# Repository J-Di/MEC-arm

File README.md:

<h1>MEC-Arm</h1>

## Overview
MEC-Arm is a six degree of freedom robotic arm which is currently being designed from scratch by 2 students team. The team is composed of a mechanical and electrical engineering student, working together to realize this shared personal project. The overall objective is to create a fully functional, precise, and practical arm, while creating many of the required components from scratch along the way. This repository contains both the mechanical and the electrical side of the project, after all, this is a **M**echanical **E**lectrical **C**ollaboration -Arm :)

Find all the Documentation here: [MEC-Arm Documentation Page](https://j-di.github.io/MEC-arm/)

### Key Features:

#### Arm
- Joint layout: waist (roll), shoulder (pitch), elbow (pitch), 3-axis wrist (roll, pitch, roll)
- Arm weight: TBD
- End effector: gripper, driven by the 7th motor
- Max joint speed: 90 RPM (shoulder)

#### Actuation

- Actuators: 7× brushless motors with custom cycloidal gearboxes
- Gear ratios: 19:1, 25:1, 15:1
- Motor control: FOC at every joint
- Position feedback: on-board magnetic encoders

#### Power & control

- Battery: 6S LiPo, 25.2–18V, TBD mA
- Communication: CAN bus 
- Host: controlled from a raspberry pi

## Timeline

```mermaid
flowchart LR
    subgraph Shared
        A[Requirements defined]
        B[Arm structure decided]
        C[Joint torque calculations]
        D[Motors sourced]
    end

    subgraph Electrical
        E[ESC design]
        H[ESC bring-up and testing]
        P[Power distribution and coordination board]
    end

    subgraph Mechanical
        F[Preliminary arm structure]
        G[Gearbox design]
        I[Joint assembly]
    end

    K[Per-joint gearbox testing]
    L[Torque characterization]
    J[Full arm integration]
    S[Software begins]

    A --> B --> C --> D
    D --> E --> H
    D --> P
    D --> F --> G --> I
    H --> K
    G --> K
    K --> L
    L --> J
    I --> J
    P --> J
    J --> S

    classDef done fill:#2da44e,stroke:#1a7f37,color:#fff
    classDef wip  fill:#d4a72c,stroke:#9a6700,color:#fff
    classDef todo fill:#8c959f,stroke:#57606a,color:#fff
    class A,B,C,D,F done
    class E,G,P wip
    class H,I,J,K,L,S todo
```

🟩 Done · 🟨 In progress · ⬜ Planned

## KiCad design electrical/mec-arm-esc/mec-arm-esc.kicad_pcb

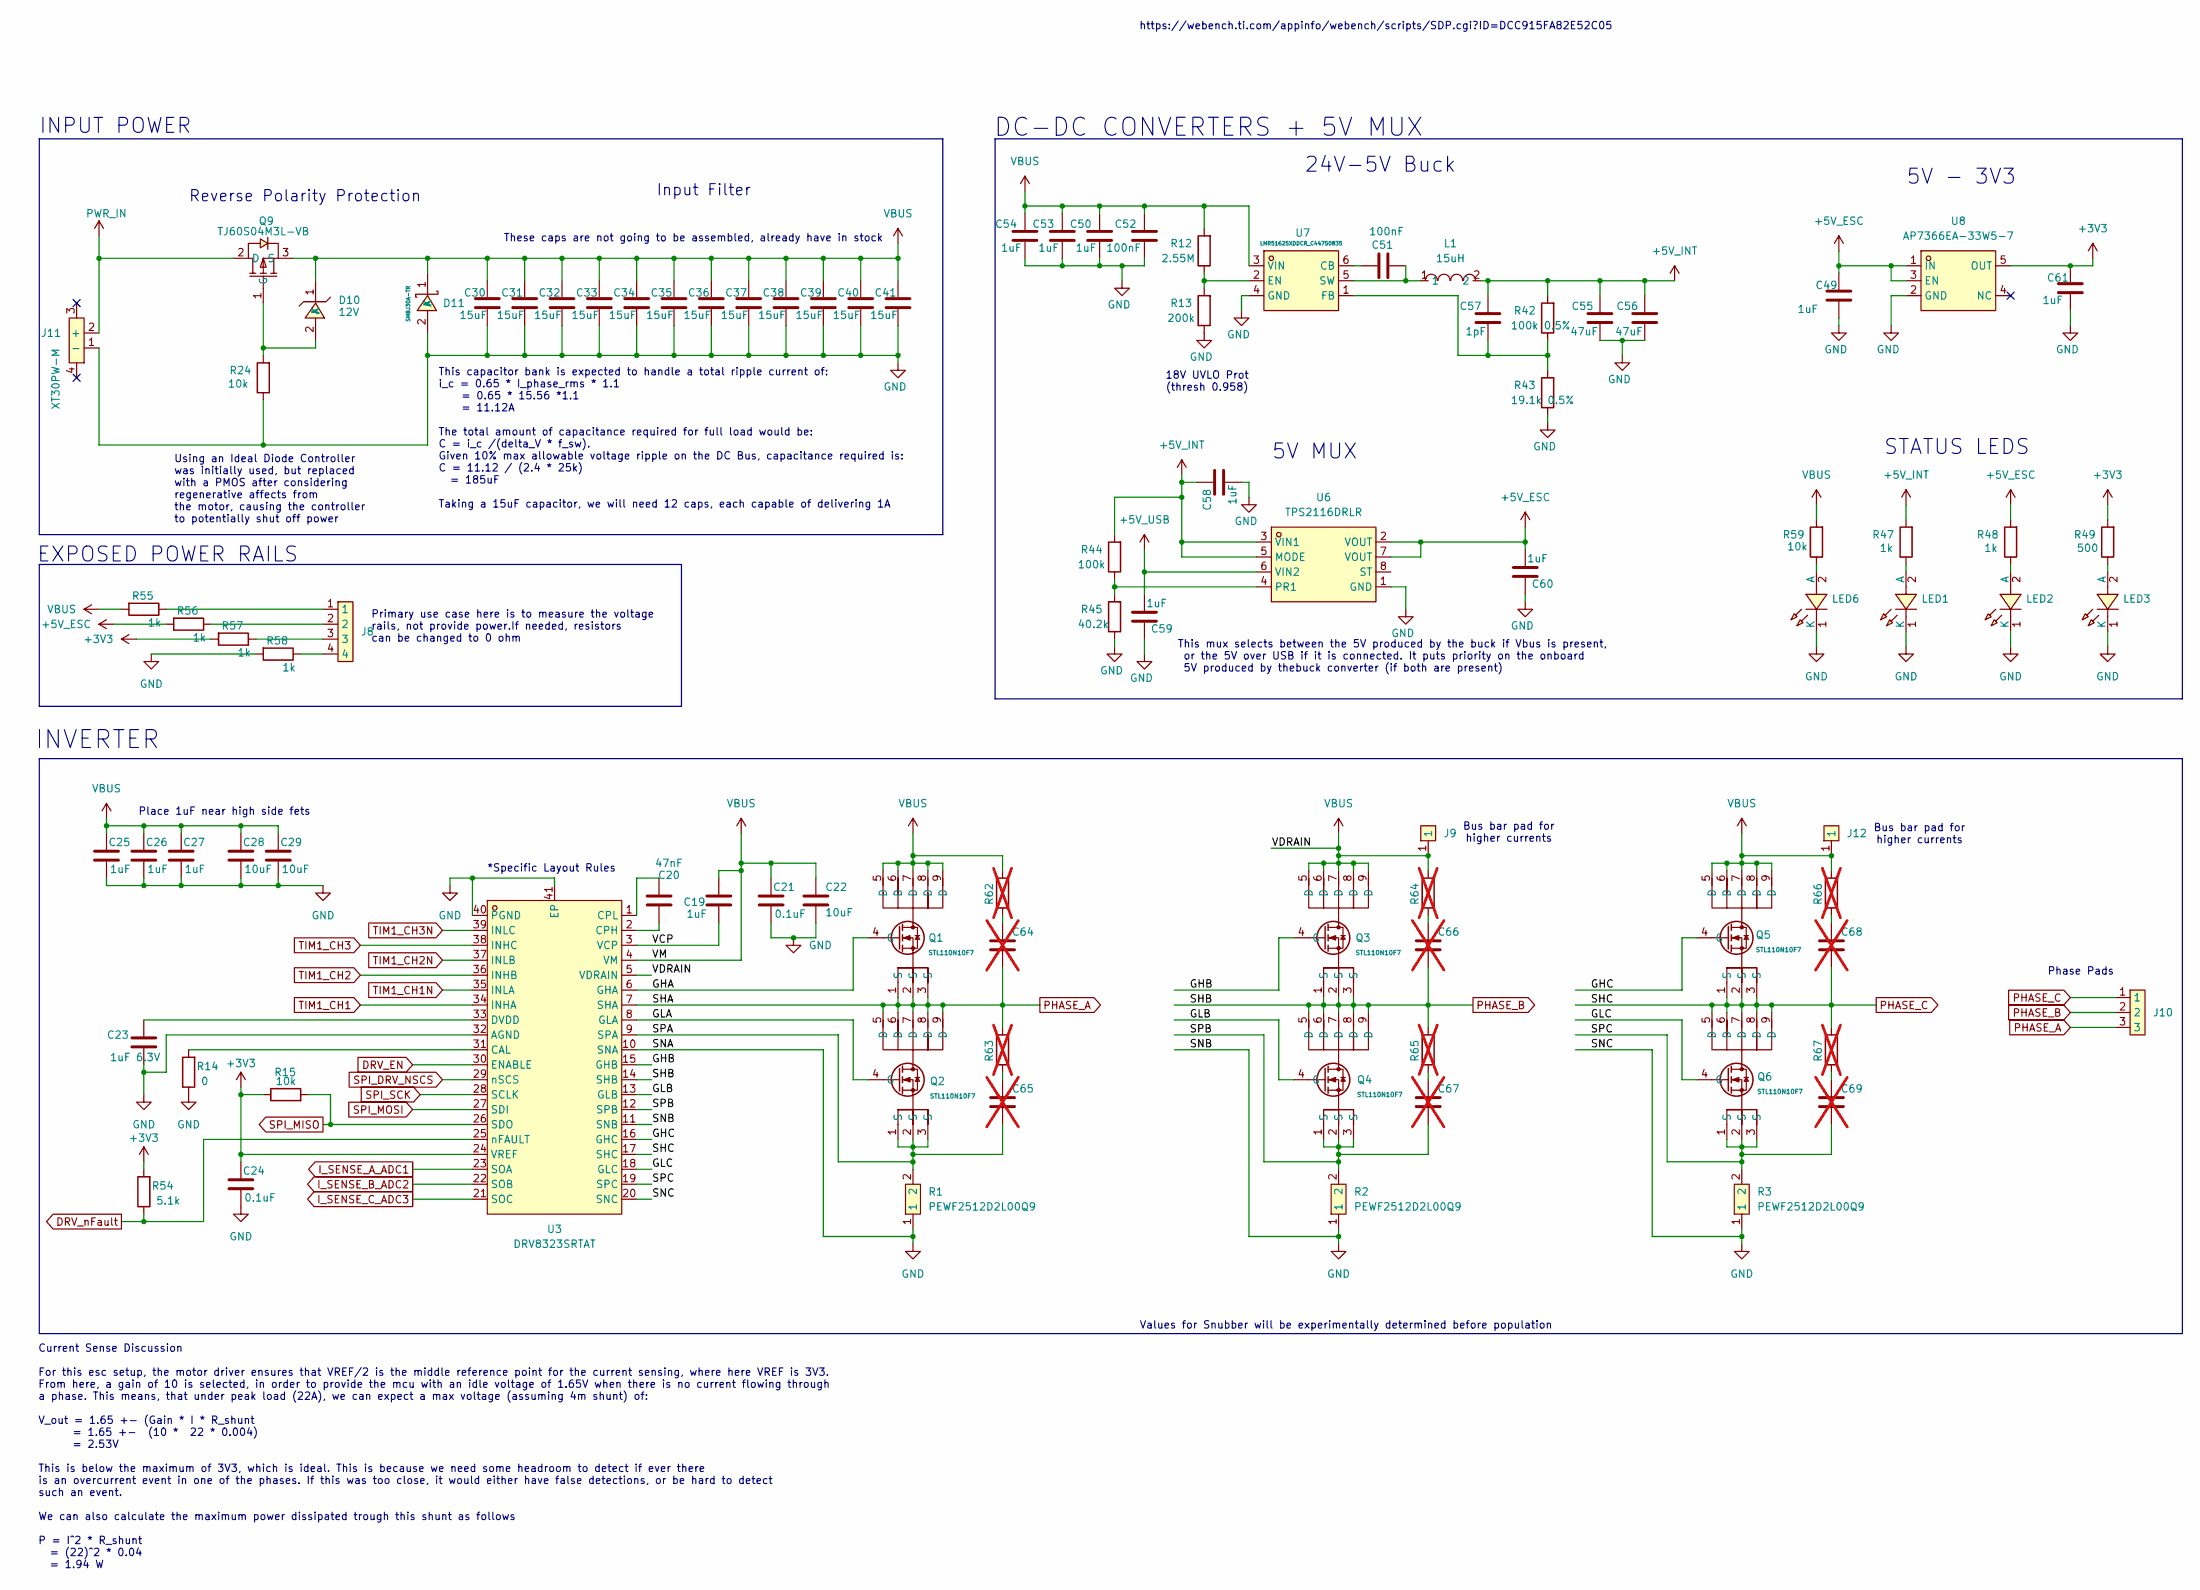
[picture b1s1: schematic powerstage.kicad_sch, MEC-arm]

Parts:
C19: 1uF; C_0603; LCSC Part C14664
C20: 47nF; C_0603; LCSC Part C513577
C21: 0.1uF; C_0603; LCSC Part C14663
C22, C28, C29: 10uF; C_0805; LCSC Part C162422
C23: 1uF 6.3V; C_0603; LCSC Part C2169508
C24: 0.1uF; C_0603; LCSC Part C108079
C25, C26, C27, C50, C53, C54: 1uF; C_0603; LCSC Part C559769
C30: 15uF; C_0805; LCSC Part# C162422
C31, C32, C33, C34, C35, C36, C37, C38, C39, C40, C41: 15uF; C_0805; LCSC Part C162422
C49, C58, C59, C60, C61: 1uF; C_0603; LCSC Part C106248
C51, C52: 100nF; C_0603; LCSC Part C14663
C55, C56: 47uF; C_1210_3225Metric; LCSC Part C77101
C57: 1pF; C_0603; LCSC Part C29936
C64, C65, C66, C67, C68, C69: 10uF; C_0603; not fitted
D10: 12V; SOD-123F_L2.8-W1.8-LS3.7-RD; MPN BZT52C12-13-F; LCSC Part C177013
D11: SMBJ30A-TR; SMB_L4.6-W3.6-LS5.3-RD; MPN SMBJ30A-TR; LCSC Part C133663
J8: TestPadArray1x4
J9: 5x3BusBar Pad
J10: PHASE_PAD
J11: XT30PW-M; CONN-TH_XT30PW-M; MPN XT30PW-M30.G.Y; LCSC Part C431092
J12: 3x3BusBar Pad
L1: 15uH; IND-SMD_L6.0-W6.0_VLS6045EX; MPN VLS6045EX-150M; LCSC Part C404502
LED1, LED2, LED3, LED6: 150060RS75000; LED0603-RD_RED; MPN 150060RS75000; LCSC Part C3030991
Q1, Q2, Q3, Q4, Q5, Q6: STL110N10F7; DFN-8_L5.8-W4.9-P1.27-LS6.0-BL-1; MPN STL110N10F7; LCSC Part C672185
Q9: TJ60S04M3L-VB; TO-252-2_L6.6-W6.1-P4.58-LS9.9-TL; MPN TJ60S04M3L-VB; LCSC Part C7494452
R1, R2, R3: PEWF2512D2L00Q9; RES-SMD_L6.3-W3.2_R2512; MPN PEWF2512D2L00Q9; LCSC Part C19697176
R12: 2.55M; R_0603; LCSC Part C54102347
R13: 200k; R_0603; LCSC Part C2907009
R14: 0; R_0603; LCSC Part C2906974
R15, R24, R59: 10k; R_0603; LCSC Part C98220
R42: 100k 0.5%; R_0603; LCSC Part C122538
R43: 19.1k 0.5%; R_0603; LCSC Part C861184
R44: 100k; R_0603; LCSC Part C2906980
R45: 40.2k; R_0603; LCSC Part C286588
R47, R48, R55, R56, R57, R58: 1k; R_0603; LCSC Part C14676
R49: 500; R_0603; LCSC Part C73811
R54: 5.1k; R_0603; LCSC Part C2907044
R62, R63, R64, R65, R66, R67: 1k; R_0603; not fitted
U3: DRV8323SRTAT; WQFN-40_L6.0-W6.0-P0.50-TL-EP4.5; MPN DRV8323SRTAT; LCSC Part C2150452
U6: TPS2116DRLR; SOT-583-8_L2.1-W1.6-P0.50-LS1.6-BL; MPN TPS2116DRLR; LCSC Part C3235557
U7: LMR51625XDDCR_C44750835; SOT-23-6_L2.9-W1.6-P0.95-LS2.9-BL; MPN LMR51625XDDCR; LCSC Part C44750835
U8: AP7366EA-33W5-7; SOT-23-5_L3.0-W1.6-P0.95-LS2.8-BR; MPN AP7366EA-33W5-7; LCSC Part C22038443

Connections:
+3V3: C24.1, C61.1, R15.1, R49.2, R54.2, R57.2, U3.24 (VREF), U8.5 (OUT); also elsewhere on the board
+5V_ESC: C49.1, C60.1, R48.2, R56.2, U6.2 (VOUT), U6.7 (VOUT), U8.1 (IN), U8.3 (EN); also elsewhere on the board
+5V_INT: C55.2, C56.2, C57.2, C58.2, L1.2, R42.2, R44.2, R47.2, U6.3 (VIN1), U6.5 (MODE)
+5V_USB: C59.1, U6.6 (VIN2); also elsewhere on the board
/powerstage/GHA: Q1.4 (G), U3.6 (GHA)
/powerstage/GHB: Q3.4 (G), U3.15 (GHB)
/powerstage/GHC: Q5.4 (G), U3.16 (GHC)
/powerstage/GLA: Q2.4 (G), U3.8 (GLA)
/powerstage/GLB: Q4.4 (G), U3.13 (GLB)
/powerstage/GLC: Q6.4 (G), U3.18 (GLC)
/powerstage/SPA: C65.2, Q2.1 (S), Q2.2 (S), Q2.3 (S), R1.2, U3.9 (SPA)
/powerstage/SPB: C67.2, Q4.1 (S), Q4.2 (S), Q4.3 (S), R2.2, U3.12 (SPB)
/powerstage/SPC: C69.2, Q6.1 (S), Q6.2 (S), Q6.3 (S), R3.2, U3.19 (SPC)
/powerstage/VCP: C19.2, U3.3 (VCP)
DRV_EN: U3.30 (ENABLE); also elsewhere on the board
DRV_nFault: R54.1, U3.25 (nFAULT); also elsewhere on the board
GND: C21.2, C22.2, C23.2, C24.2, C25.2, C26.2, C27.2, C28.2, C29.2, C30.2, C31.2, C32.2, C33.2, C34.2, C35.2, C36.2, C37.2, C38.2, C39.2, C40.2, C41.2, C49.2, C50.1, C52.1, C53.1, C54.1, C55.1, C56.1, C58.1, C59.2, C60.2, C61.2, D11.2 (A), J11.1 (-), LED1.1 (K), LED2.1 (K), LED3.1 (K), LED6.1 (K), R1.1, R2.1, R3.1, R13.1, R14.1, R24.1, R43.1, R45.1, R58.2, U3.10 (SNA), U3.11 (SNB), U3.20 (SNC), U3.32 (AGND), U3.40 (PGND), U3.41 (EP), U6.1 (GND), U7.4 (GND), U8.2 (GND); also elsewhere on the board
I_SENSE_A_ADC1: U3.23 (SOA); also elsewhere on the board
I_SENSE_B_ADC2: U3.22 (SOB); also elsewhere on the board
I_SENSE_C_ADC3: U3.21 (SOC); also elsewhere on the board
unnamed: C64.1, R62.2
unnamed: C65.1, R63.2
unnamed: C66.1, R64.2
unnamed: C67.1, R65.2
unnamed: C68.1, R66.2
unnamed: C69.1, R67.2
unnamed: D10.2 (A), Q9.1 (G), R24.2
unnamed: J8.1, R55.1
unnamed: J8.2, R56.1
unnamed: J8.3, R57.1
unnamed: J8.4, R58.1
unnamed: LED1.2 (A), R47.1
unnamed: LED2.2 (A), R48.1
unnamed: LED3.2 (A), R49.1
unnamed: LED6.2 (A), R59.1
unnamed: R14.2, U3.31 (CAL)
unnamed: C20.2, U3.2 (CPH)
unnamed: C20.1, U3.1 (CPL)
unnamed: C23.1, U3.33 (DVDD)
unnamed: R44.1, R45.2, U6.4 (PR1)
unnamed: C51.1, U7.6 (CB)
unnamed: R12.1, R13.2, U7.2 (EN)
unnamed: C57.1, R42.1, R43.2, U7.1 (FB)
unnamed: C51.2, L1.1, U7.5 (SW)
PHASE_A: C64.2, J10.3, Q1.1 (S), Q1.2 (S), Q1.3 (S), Q2.5 (D), Q2.6 (D), Q2.7 (D), Q2.8 (D), Q2.9 (D), R63.1, U3.7 (SHA)
PHASE_B: C66.2, J10.2, Q3.1 (S), Q3.2 (S), Q3.3 (S), Q4.5 (D), Q4.6 (D), Q4.7 (D), Q4.8 (D), Q4.9 (D), R65.1, U3.14 (SHB)
PHASE_C: C68.2, J10.1, Q5.1 (S), Q5.2 (S), Q5.3 (S), Q6.5 (D), Q6.6 (D), Q6.7 (D), Q6.8 (D), Q6.9 (D), R67.1, U3.17 (SHC)
PWR_IN: J11.2 (+), Q9.2 (D)
SPI_DRV_NSCS: U3.29 (nSCS); also elsewhere on the board
SPI_MISO: R15.2, U3.26 (SDO); also elsewhere on the board
SPI_MOSI: U3.27 (SDI); also elsewhere on the board
SPI_SCK: U3.28 (SCLK); also elsewhere on the board
TIM1_CH1: U3.34 (INHA); also elsewhere on the board
TIM1_CH1N: U3.35 (INLA); also elsewhere on the board
TIM1_CH2: U3.36 (INHB); also elsewhere on the board
TIM1_CH2N: U3.37 (INLB); also elsewhere on the board
TIM1_CH3: U3.38 (INHC); also elsewhere on the board
TIM1_CH3N: U3.39 (INLC); also elsewhere on the board
VBUS: C19.1, C21.1, C22.1, C25.1, C26.1, C27.1, C28.1, C29.1, C30.1, C31.1, C32.1, C33.1, C34.1, C35.1, C36.1, C37.1, C38.1, C39.1, C40.1, C41.1, C50.2, C52.2, C53.2, C54.2, D10.1 (K), D11.1 (K), J9.1 (1_1), J12.1 (1_1), Q1.5 (D), Q1.6 (D), Q1.7 (D), Q1.8 (D), Q1.9 (D), Q3.5 (D), Q3.6 (D), Q3.7 (D), Q3.8 (D), Q3.9 (D), Q5.5 (D), Q5.6 (D), Q5.7 (D), Q5.8 (D), Q5.9 (D), Q9.3 (S), R12.2, R55.2, R59.2, R62.1, R64.1, R66.1, U3.4 (VM), U3.5 (VDRAIN), U7.3 (VIN); also elsewhere on the board

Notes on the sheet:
*Specific Layout Rules
These caps are not going to be assembled, already have in stock
This mux selects between the 5V produced by the buck if Vbus is present, or the 5V over USB if it is connected. It puts priority on the onboard 5V produced by thebuck converter (if both are present)
Primary use case here is to measure the voltage rails, not provide power.If needed, resistors can be changed to 0 ohm
INPUT POWER
DC-DC CONVERTERS + 5V MUX
EXPOSED POWER RAILS
Place 1uF near high side fets
Values for Snubber will be experimentally determined before population
INVERTER
Current Sense Discussion For this esc setup, the motor driver ensures that VREF/2 is the middle reference point for the current sensing, where here VREF is 3V3. From here, a gain of 10 is selected, in order to provide the mcu with an idle voltage of 1.65V when there is no current flowing through a 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
This capacitor bank is expected to handle a total ripple current of: i_c = 0.65 * I_phase_rms * 1.1 = 0.65 * 15.56 *1.1 = 11.12A The total amount of capacitance required for full load would be: C = i_c /(delta_V * f_sw). Given 10% max allowable voltage ripple on the DC Bus, capacitance required is: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
STATUS LEDS
18V UVLO Prot (thresh 0.958)
5V MUX
Bus bar pad for higher currents
Phase Pads
Input Filter
Using an Ideal Diode Controller was initially used, but replaced with a PMOS after considering regenerative affects from the motor, causing the controller to potentially shut off power
5V - 3V3
Reverse Polarity Protection
https://webench.ti.com/appinfo/webench/scripts/SDP.cgi?ID=DCC915FA82E52C05
24V-5V Buck

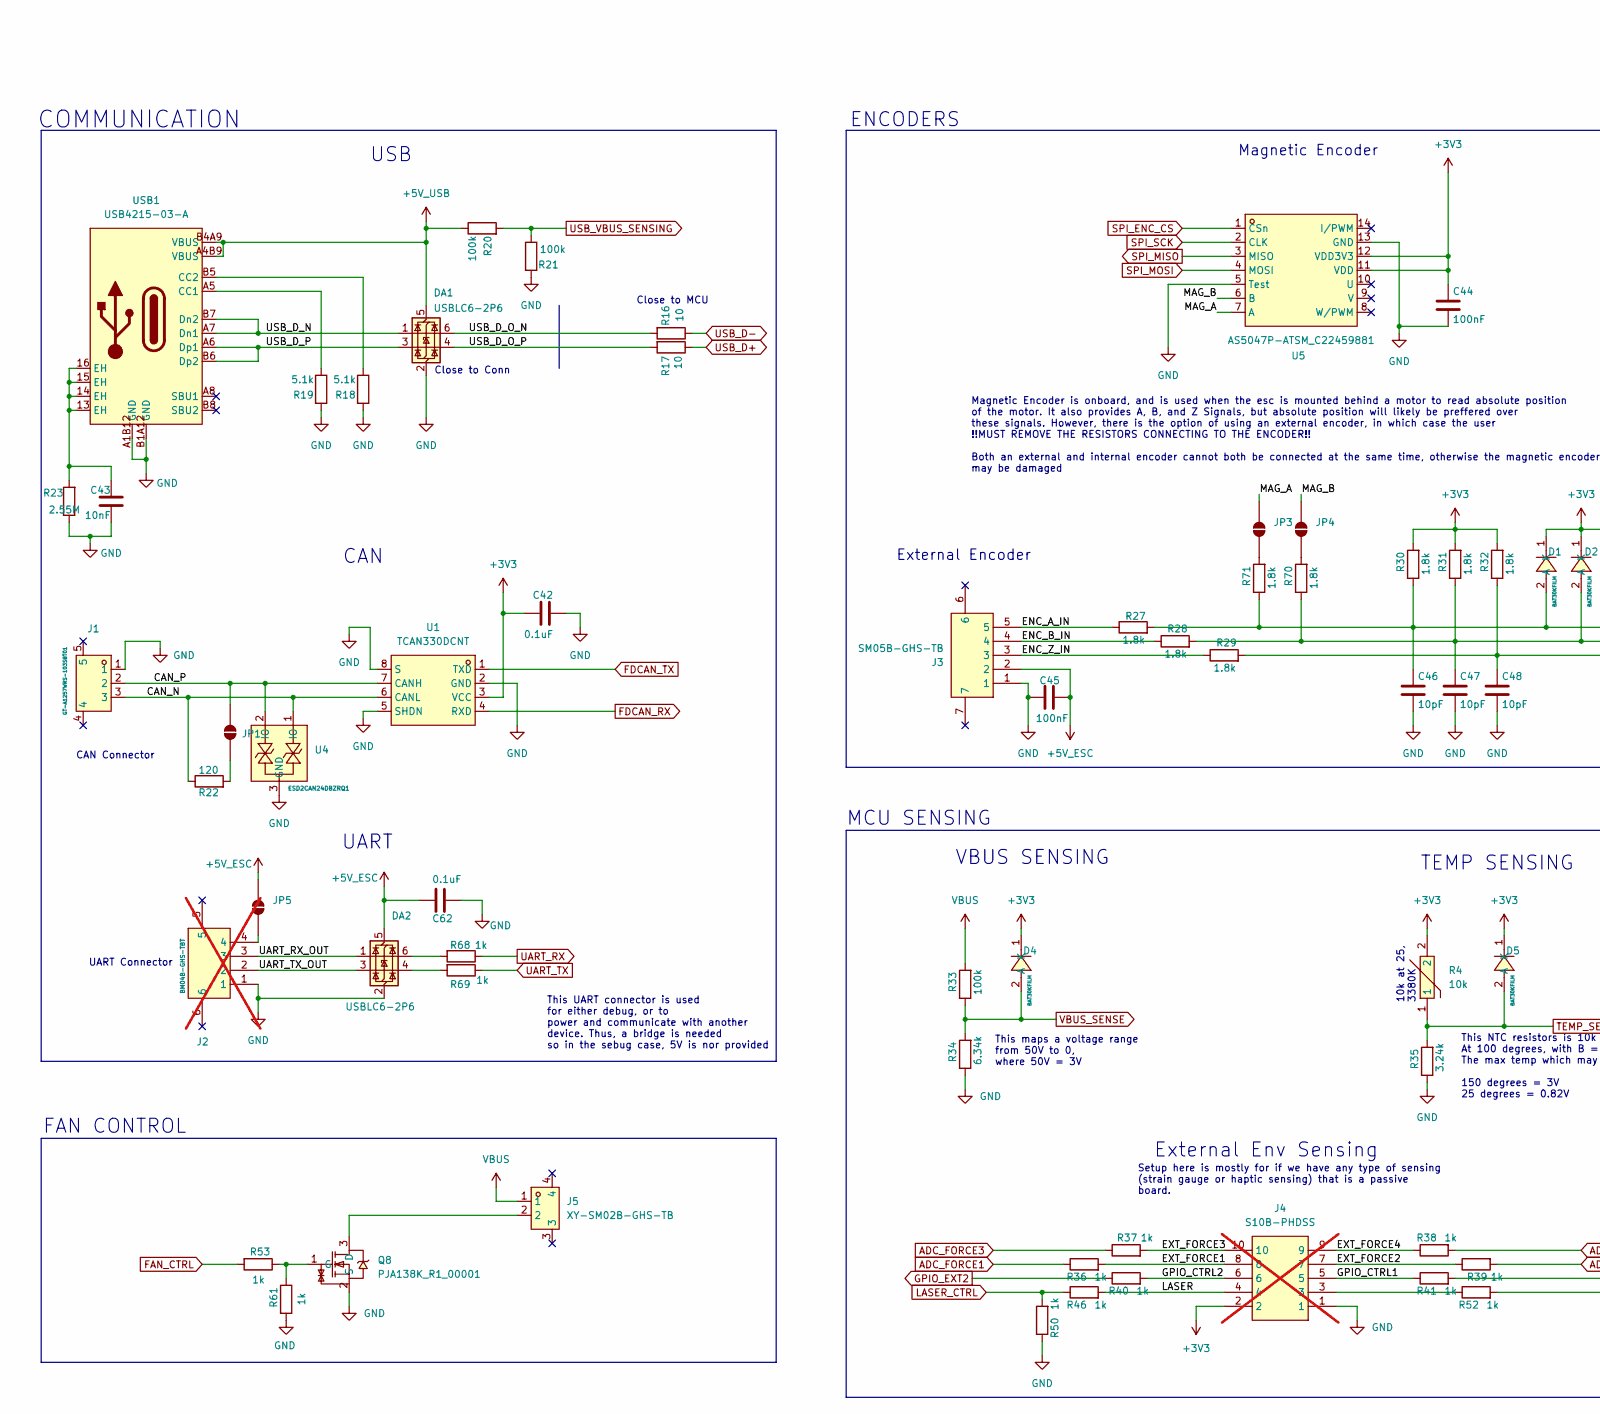
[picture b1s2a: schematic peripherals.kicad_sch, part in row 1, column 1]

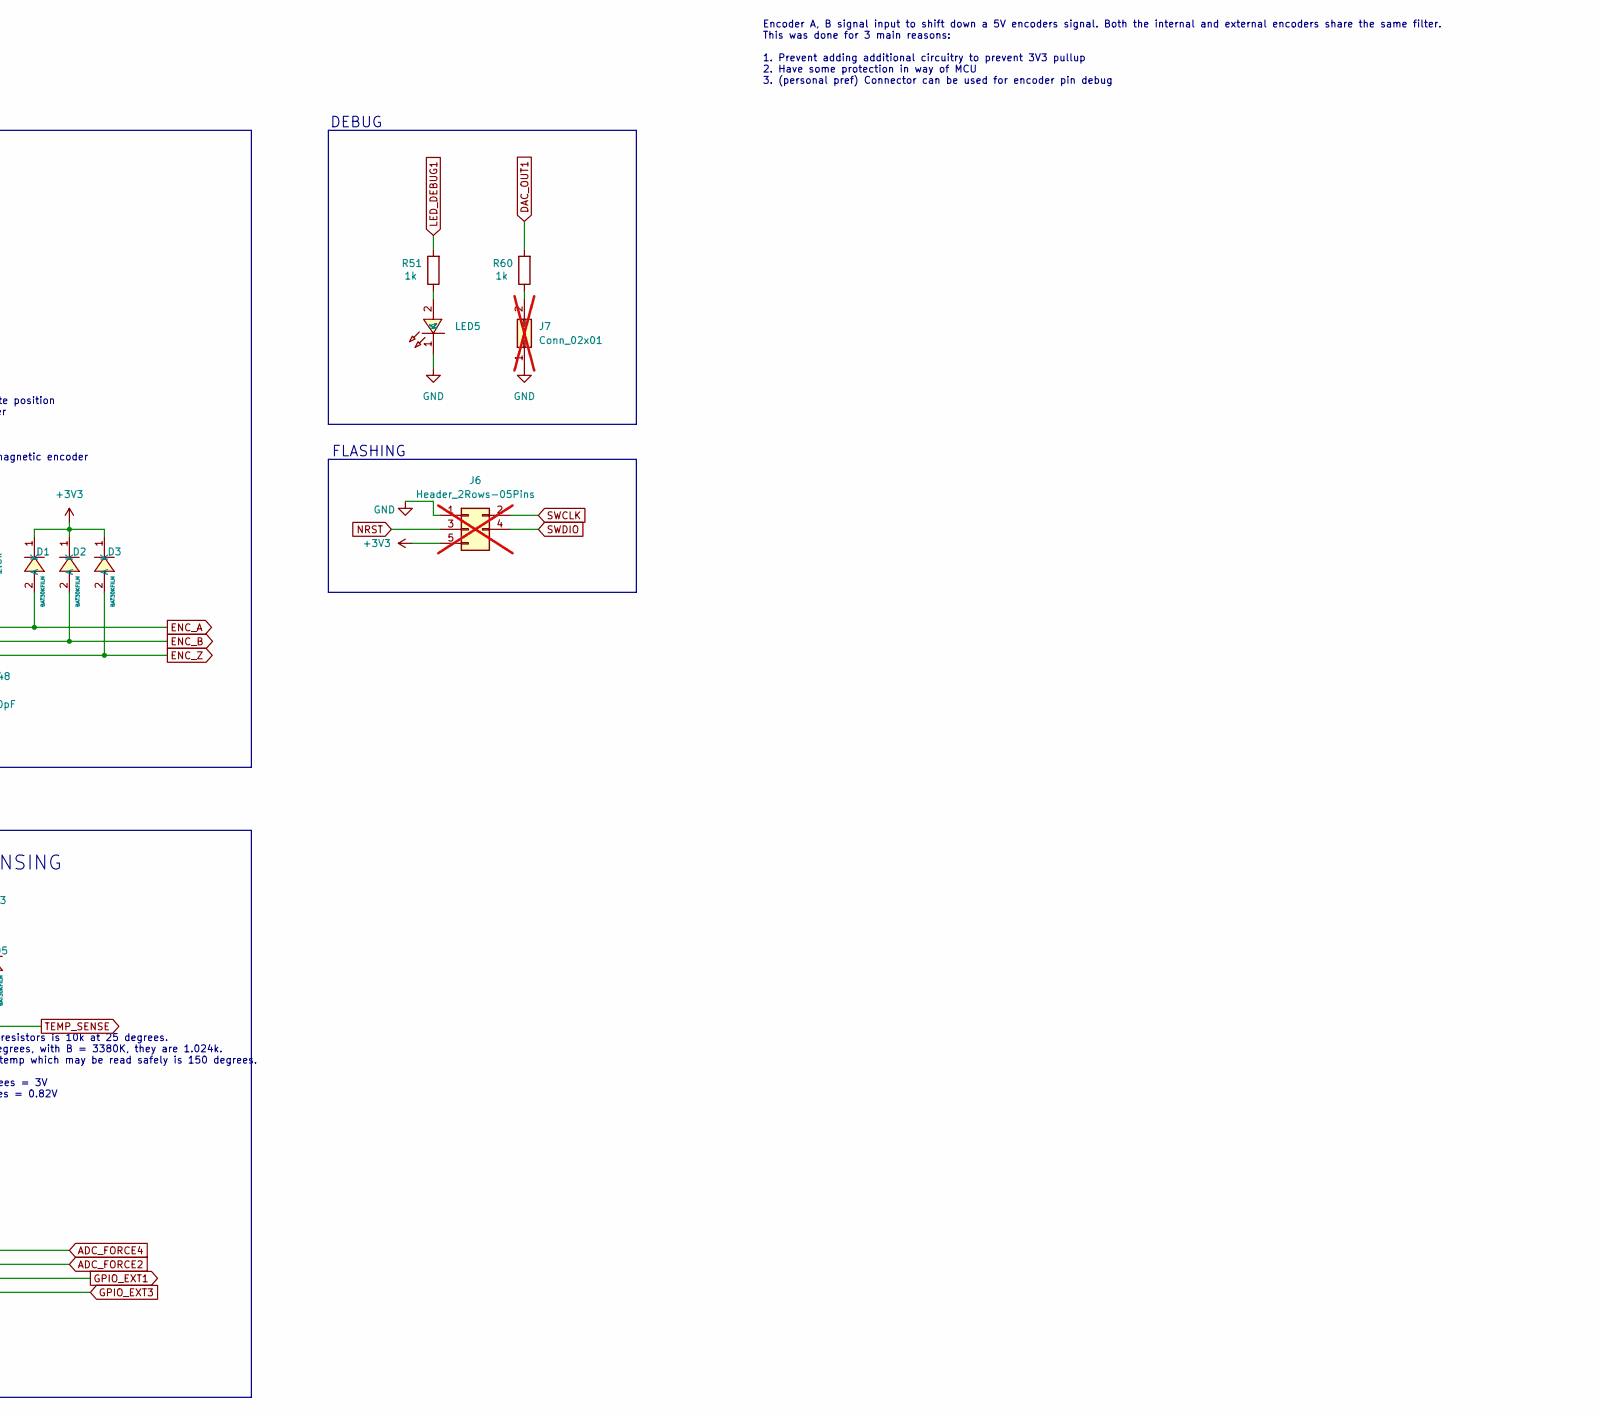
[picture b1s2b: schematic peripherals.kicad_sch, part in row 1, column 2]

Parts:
C42, C62: 0.1uF; C_0603; LCSC Part C108079
C43: 10nF; C_0603; LCSC Part C519406
C44, C45: 100nF; C_0603; LCSC Part C108079
C46, C47, C48: 10pF; C_0603; LCSC Part C2168592
D1, D2, D3, D4, D5: BAT30KFILM; SOD-523_L1.2-W0.8-LS1.6-RD-1; MPN BAT30KFILM; LCSC Part C2926449
DA1, DA2: USBLC6-2P6; SOT-666-6_L1.6-W1.2-P0.50-LS1.6-BR; MPN USBLC6-2P6; LCSC Part C15999
J1: GT-A1257WRS-103SBT01; CONN-SMD_GT-A1257WRS-103SBT01; MPN GT-A1257WRS-103SBT01; LCSC Part C22472755
J2: BM04B-GHS-TBT; CONN-SMD_4P-P1.25_BM04B-GHS-TBT-LF-SN; MPN BM04B-GHS-TBT(LF)(SN); LCSC Part C161692; not fitted
J3: SM05B-GHS-TB; CONN-SMD_5P-P1.25_SM05B-GHS-TB-LF-SN; MPN SM05B-GHS-TB(LF)(SN); LCSC Part C189896
J4: S10B-PHDSS; CONN-TH_S10B-PHDSS-LF-SN; MPN S10B-PHDSS(LF)(SN); LCSC Part C161672; not fitted
J5: XY-SM02B-GHS-TB; CONN-SMD_SM02B-GHS-TB-LF-SN; MPN XY-SM02B-GHS-TB; LCSC Part C54582897
J6: Header_2Rows-05Pins; PinHeader_2_row_5_pin_P2.54mm_Vertical; not fitted
J7: Conn_02x01; PinHeader_1x02_P2.54mm_Vertical; not fitted
JP1, JP3, JP4, JP5: SolderJumper_2_Open; SolderJumper-2_P1.3mm_Open_TrianglePad1.0x1.5mm
LED5: LTST-C171KGKT; LED0805-RD; MPN LTST-C171KGKT; LCSC Part C98224
Q8: PJA138K_R1_00001; SOT-23_L2.9-W1.3-P1.90-LS2.4-BR; MPN PJA138K_R1_00001; LCSC Part C2902548
R4: 10k; R0603; MPN ERTJ1VG103FA; LCSC Part C153011
R16, R17: 10; R_0603; LCSC Part C844919
R18, R19: 5.1k; R_0603; LCSC Part C2907044
R20, R21, R33: 100k; R_0603; LCSC Part C2906980
R22: 120; R_0603; LCSC Part C2906988
R23: 2.55M; R_0603; LCSC Part C54102347
R27, R28, R29, R30, R31, R32, R70, R71: 1.8k; R_0603; LCSC Part C286575
R34: 6.34k; R_0603; LCSC Part C321969
R35: 3.24k; R_0603; LCSC Part C728589
R36, R37, R38, R39, R40, R41, R46, R50, R51, R52, R53, R60, R61, R68, R69: 1k; R_0603; LCSC Part C14676
U1: TCAN330DCNT; SOT-23-8_L2.9-W1.6-P0.65-LS2.8-BR; MPN TCAN330DCNT; LCSC Part C2671056
U4: ESD2CAN24DBZRQ1; SOT-23-3_L2.9-W1.3-P1.90-LS2.4-BR; MPN ESD2CAN24DBZRQ1; LCSC Part C5736151
U5: AS5047P-ATSM_C22459881; TSSOP-14_L5.0-W4.4-P0.65-LS6.4-BL; MPN AS5047P-ATSM; LCSC Part C22459881
USB1: USB4215-03-A; USB-C-SMD_GT-USB-7010B; MPN USB4215-03-A; LCSC Part C37616412

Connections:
+3V3: C42.1, C44.1, D1.1 (K), D2.1 (K), D3.1 (K), D4.1 (K), D5.1 (K), J4.2, J6.5, R4.2, R30.2, R31.2, R32.2, U1.3 (VCC), U5.11 (VDD), U5.12 (VDD3V3); also elsewhere on the board
+5V_ESC: C45.2, C62.2, DA2.5 (VBUS), J3.2, JP5.2 (B); also elsewhere on the board
+5V_USB: DA1.5 (VBUS), R20.1, USB1.A4B9 (VBUS), USB1.B4A9 (VBUS); also elsewhere on the board
/peripherals/CAN_N: J1.3, R22.1, U1.6 (CANL), U4.1 (IO)
/peripherals/CAN_P: J1.2, JP1.2 (B), U1.7 (CANH), U4.2 (IO)
/peripherals/ENC_A_IN: J3.5, R27.1
/peripherals/ENC_B_IN: J3.4, R28.1
/peripherals/ENC_Z_IN: J3.3, R29.1
/peripherals/EXT_FORCE1: J4.8, R36.2
/peripherals/EXT_FORCE2: J4.7, R39.1
/peripherals/EXT_FORCE3: J4.10, R37.2
/peripherals/EXT_FORCE4: J4.9, R38.1
/peripherals/GPIO_CTRL1: J4.5, R41.1
/peripherals/GPIO_CTRL2: J4.6, R40.2
/peripherals/LASER: J4.4, R46.2
/peripherals/MAG_A: JP3.2 (B), U5.7 (A)
/peripherals/MAG_B: JP4.2 (B), U5.6 (B)
/peripherals/UART_RX_OUT: DA2.1 (I/O1), J2.3
/peripherals/UART_TX_OUT: DA2.3 (I/O2), J2.2
/peripherals/USB_D_N: DA1.1 (I/O1), USB1.A7 (Dn1), USB1.B7 (Dn2)
/peripherals/USB_D_O_N: DA1.6 (I/O1), R16.2
/peripherals/USB_D_O_P: DA1.4 (I/O2), R17.2
/peripherals/USB_D_P: DA1.3 (I/O2), USB1.A6 (Dp1), USB1.B6 (Dp2)
ADC_FORCE1: R36.1; also elsewhere on the board
ADC_FORCE2: R39.2; also elsewhere on the board
ADC_FORCE3: R37.1; also elsewhere on the board
ADC_FORCE4: R38.2; also elsewhere on the board
DAC_OUT1: R60.2; also elsewhere on the board
ENC_A: C46.1, D1.2 (A), R27.2, R30.1, R71.1; also elsewhere on the board
ENC_B: C47.1, D2.2 (A), R28.2, R31.1, R70.1; also elsewhere on the board
ENC_Z: C48.1, D3.2 (A), R29.2, R32.1; also elsewhere on the board
FAN_CTRL: R53.2; also elsewhere on the board
FDCAN_RX: U1.4 (RXD); also elsewhere on the board
FDCAN_TX: U1.1 (TXD); also elsewhere on the board
GND: C42.2, C43.1, C44.2, C45.1, C46.2, C47.2, C48.2, C62.1, DA1.2 (GND), DA2.2 (GND), J1.1, J2.1, J3.1, J4.1, J6.1, J7.1, LED5.1 (K), Q8.2 (S), R18.2, R19.2, R21.2, R23.1, R34.1, R35.1, R50.1, R61.2, U1.2 (GND), U1.5 (SHDN), U1.8 (S), U4.3 (GND), U5.5 (Test), U5.13 (GND), USB1.A1B12 (GND), USB1.B1A12 (GND); also elsewhere on the board
GPIO_EXT1: R41.2; also elsewhere on the board
GPIO_EXT2: R40.1; also elsewhere on the board
GPIO_EXT3: R52.2; also elsewhere on the board
LASER_CTRL: R46.1, R50.2; also elsewhere on the board
LED_DEBUG1: R51.2; also elsewhere on the board
NRST: J6.3; also elsewhere on the board
unnamed: C43.2, R23.2, USB1.13 (EH), USB1.14 (EH), USB1.15 (EH), USB1.16 (EH)
unnamed: DA2.6 (I/O1), R68.2
unnamed: DA2.4 (I/O2), R69.2
unnamed: J4.3, R52.1
unnamed: J7.2, R60.1
unnamed: JP1.1 (A), R22.2
unnamed: JP3.1 (A), R71.2
unnamed: JP4.1 (A), R70.2
unnamed: J2.4, JP5.1 (A)
unnamed: LED5.2 (A), R51.1
unnamed: J5.2, Q8.3 (D)
unnamed: Q8.1 (G), R53.1, R61.1
unnamed: R19.1, USB1.A5 (CC1)
unnamed: R18.1, USB1.B5 (CC2)
SPI_ENC_CS: U5.1 (CSn); also elsewhere on the board
SPI_MISO: U5.3 (MISO); also elsewhere on the board
SPI_MOSI: U5.4 (MOSI); also elsewhere on the board
SPI_SCK: U5.2 (CLK); also elsewhere on the board
SWCLK: J6.2; also elsewhere on the board
SWDIO: J6.4; also elsewhere on the board
TEMP_SENSE: D5.2 (A), R4.1, R35.2; also elsewhere on the board
UART_RX: R68.1; also elsewhere on the board
UART_TX: R69.1; also elsewhere on the board
USB_D+: R17.1; also elsewhere on the board
USB_D-: R16.1; also elsewhere on the board
USB_VBUS_SENSING: R20.2, R21.1; also elsewhere on the board
VBUS: J5.1, R33.2; also elsewhere on the board
VBUS_SENSE: D4.2 (A), R33.1, R34.2; also elsewhere on the board

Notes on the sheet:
External Encoder
This NTC resistors is 10k at 25 degrees. At 100 degrees, with B = 3380K, they are 1.024k. The max temp which may be read safely is 150 degrees. 150 degrees = 3V 25 degrees = 0.82V
This maps a voltage range from 50V to 0, where 50V = 3V
Magnetic Encoder
UART
This UART connector is used for either debug, or to power and communicate with another device. Thus, a bridge is needed so in the sebug case, 5V is nor provided
FLASHING
Close to Conn
ENCODERS
COMMUNICATION
TEMP SENSING
FAN CONTROL
Encoder A, B signal input to shift down a 5V encoders signal. Both the internal and external encoders share the same filter. This was done for 3 main reasons: 1. Prevent adding additional circuitry to prevent 3V3 pullup 2. Have some protection in way of MCU 3. (personal pref) Connector can be used 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
External Env Sensing
Setup here is mostly for if we have any type of sensing (strain gauge or haptic sensing) that is a passive board.
MCU SENSING
USB
Magnetic Encoder is onboard, and is used when the esc is mounted behind a motor to read absolute position of the motor. It also provides A, B, and Z Signals, but absolute position will likely be preffered over these signals. However, there is the option of using an external encoder, in which case t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
10k at 25, 3380K
VBUS SENSING
DEBUG
UART Connector
Close to MCU
CAN
CAN Connector

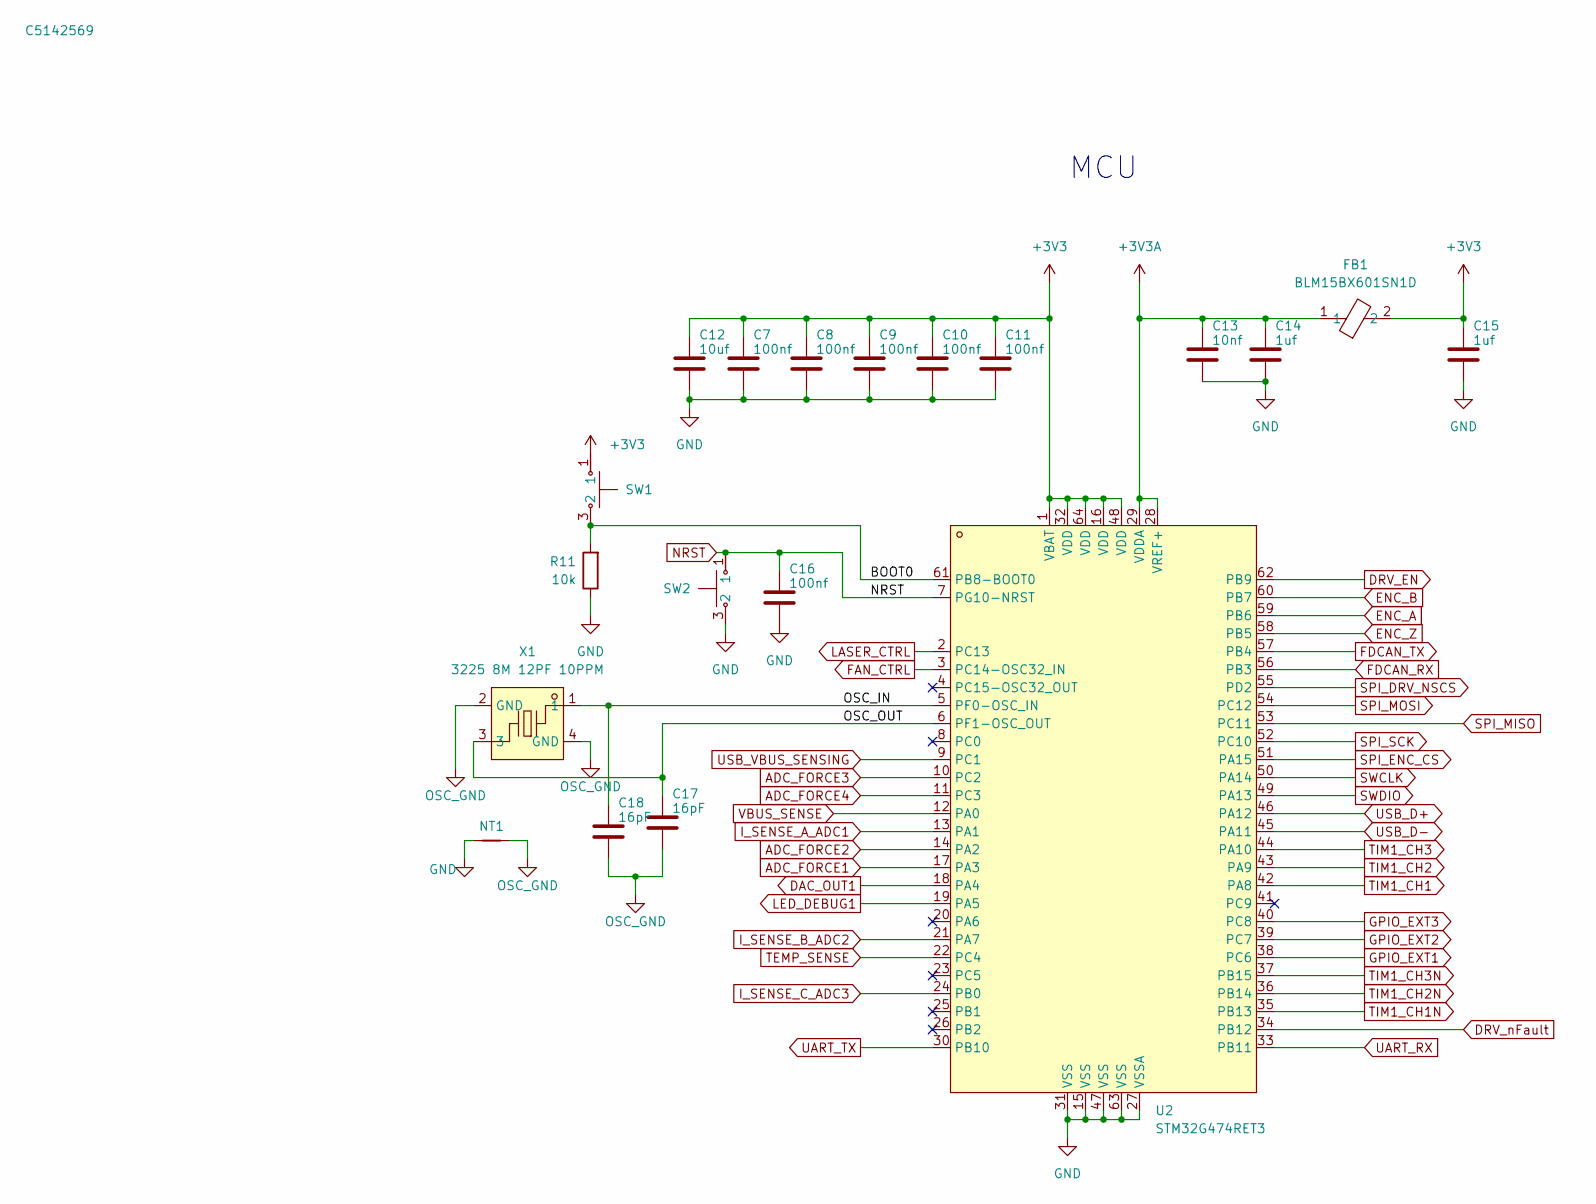
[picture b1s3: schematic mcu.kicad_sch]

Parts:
C7, C8, C9, C10, C11, C16: 100nf; C_0603; LCSC Part C108079
C12: 10uf; C_0805; LCSC Part C711098
C13: 10nf; C_0603; LCSC Part C519406
C14, C15: 1uf; C_0603; LCSC Part C106248
C17, C18: 16pF; C_0402_1005Metric; LCSC Part C5142569
FB1: BLM15BX601SN1D; L0402; MPN BLM15BX601SN1D; LCSC Part C710336
NT1: NetTie_2; NetTie-2_SMD_Pad0.5mm
R11: 10k; R_0603; LCSC Part C98220
SW1, SW2: SH-1808SN-250GF; SW-SMD_4P-L4.2-W3.4-P2.15-LS5.2; MPN SH-1808SN-250gf; LCSC Part C52092028
U2: STM32G474RET3; LQFP-64_L10.0-W10.0-P0.50-LS12.0-BL; MPN STM32G474RET3; LCSC Part C1236669
X1: 3225 8M 12PF 10PPM; CRYSTAL-SMD_4P-L3.2-W2.5-BL; MPN 3225 8M 12PF 10PPM; LCSC Part C5181478

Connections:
+3V3: C7.1, C8.1, C9.1, C10.1, C11.1, C12.1, C15.1, FB1.2, SW1.1, SW1.2, U2.1 (VBAT), U2.16 (VDD), U2.32 (VDD), U2.48 (VDD), U2.64 (VDD); also elsewhere on the board
+3V3A: C13.1, C14.1, FB1.1, U2.28 (VREF+), U2.29 (VDDA)
/mcu/BOOT0: R11.2, SW1.3 (2), SW1.4, U2.61 (PB8-BOOT0)
/mcu/OSC_IN: C18.1, U2.5 (PF0-OSC_IN), X1.1
/mcu/OSC_OUT: C17.1, U2.6 (PF1-OSC_OUT), X1.3
ADC_FORCE1: U2.17 (PA3); also elsewhere on the board
ADC_FORCE2: U2.14 (PA2); also elsewhere on the board
ADC_FORCE3: U2.10 (PC2); also elsewhere on the board
ADC_FORCE4: U2.11 (PC3); also elsewhere on the board
DAC_OUT1: U2.18 (PA4); also elsewhere on the board
DRV_EN: U2.62 (PB9); also elsewhere on the board
DRV_nFault: U2.34 (PB12); also elsewhere on the board
ENC_A: U2.59 (PB6); also elsewhere on the board
ENC_B: U2.60 (PB7); also elsewhere on the board
ENC_Z: U2.58 (PB5); also elsewhere on the board
FAN_CTRL: U2.3 (PC14-OSC32_IN); also elsewhere on the board
FDCAN_RX: U2.56 (PB3); also elsewhere on the board
FDCAN_TX: U2.57 (PB4); also elsewhere on the board
GND: C7.2, C8.2, C9.2, C10.2, C11.2, C12.2, C13.2, C14.2, C15.2, C16.2, NT1.1, R11.1, SW2.3 (2), SW2.4, U2.15 (VSS), U2.27 (VSSA), U2.31 (VSS), U2.47 (VSS), U2.63 (VSS); also elsewhere on the board
GPIO_EXT1: U2.38 (PC6); also elsewhere on the board
GPIO_EXT2: U2.39 (PC7); also elsewhere on the board
GPIO_EXT3: U2.40 (PC8); also elsewhere on the board
I_SENSE_A_ADC1: U2.13 (PA1); also elsewhere on the board
I_SENSE_B_ADC2: U2.21 (PA7); also elsewhere on the board
I_SENSE_C_ADC3: U2.24 (PB0); also elsewhere on the board
LASER_CTRL: U2.2 (PC13); also elsewhere on the board
LED_DEBUG1: U2.19 (PA5); also elsewhere on the board
NRST: C16.1, SW2.1, SW2.2, U2.7 (PG10-NRST); also elsewhere on the board
OSC_GND: C17.2, C18.2, NT1.2, X1.2 (GND), X1.4 (GND)
SPI_DRV_NSCS: U2.55 (PD2); also elsewhere on the board
SPI_ENC_CS: U2.51 (PA15); also elsewhere on the board
SPI_MISO: U2.53 (PC11); also elsewhere on the board
SPI_MOSI: U2.54 (PC12); also elsewhere on the board
SPI_SCK: U2.52 (PC10); also elsewhere on the board
SWCLK: U2.50 (PA14); also elsewhere on the board
SWDIO: U2.49 (PA13); also elsewhere on the board
TEMP_SENSE: U2.22 (PC4); also elsewhere on the board
TIM1_CH1: U2.42 (PA8); also elsewhere on the board
TIM1_CH1N: U2.35 (PB13); also elsewhere on the board
TIM1_CH2: U2.43 (PA9); also elsewhere on the board
TIM1_CH2N: U2.36 (PB14); also elsewhere on the board
TIM1_CH3: U2.44 (PA10); also elsewhere on the board
TIM1_CH3N: U2.37 (PB15); also elsewhere on the board
UART_RX: U2.33 (PB11); also elsewhere on the board
UART_TX: U2.30 (PB10); also elsewhere on the board
USB_D+: U2.46 (PA12); also elsewhere on the board
USB_D-: U2.45 (PA11); also elsewhere on the board
USB_VBUS_SENSING: U2.9 (PC1); also elsewhere on the board
VBUS_SENSE: U2.12 (PA0); also elsewhere on the board

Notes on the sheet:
MCU

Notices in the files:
firmware/mec-arm-firmware/Core/Src/tim.c:
Copyright (c) 2026 STMicroelectronics.
All rights reserved.
This software is licensed under terms that can be found in the LICENSE file
